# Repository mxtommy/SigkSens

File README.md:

# DEPRECEATED
# DEPRECEATED
Hi! This package does not have active maintenance. Please see [SensESP](https://github.com/SignalK/SensESP) for a more actively developed solution. :)
# DEPRECEATED
# DEPRECEATED

# SignalK Wifi Controllers
(Note: complete documentation is now available on the [Wiki page](https://github.com/mxtommy/SigkSens/wiki).)

## Design Goals
---------------------
Simple low cost Wifi based IoT device. Should be simple enough to setup/use that it could be manufactured and sold to people with no microcontroller/circuit design knowledge. Support configuration via a Web application, and network discovery for ease of use.

Assuming it will be installed close to the object being monitored/controlled, it should not need to support many IO by default. Aim to cover 80% of use cases with single device, assuming other 20% can be solved by adding a additional stand alone devices. If 80% of the time you only need 2 Inputs, the 20% of the time you need 4 inputs just put another device. IE prefer multiple cheap devices vs. one expensive do everything one.

Hardware should be easy to assemble on breadboard, as well as be able to be made into a PCB.

Device should send data to SignalK Server over Wifi.
Device should accept commands from Wifi. (WIP: how?)

## Use Case and Inputs required 
---------------------

- Engine Monitor
    - 1Wire Bus (multiple Temps)
    - 1 Digital Input (rpm pulse)
    - SHT30 (Engine room temp/humidity)
    - 1 Analog Inputs (Oil Presure)
- Bilge pump Monitor:
    - 2 Digital Input (Bilge pump on/off, High water Alarm)
- Fridge Monitor:
    - 1Wire Bus (Temps)
    - 1 Digital Input (Compressor on/off)
    - SHT30, Temp/Humidity
- Tank Monitor:
    - 1 Analog Input (Tank level)
- DC Monitor:
    - 1Wire Bus (Battery Temps)
    - 2 Analog Inputs - Current/Voltage 
- AC Monitor:
    - 2 Analog inputs - Current/Voltage
- GPS
    - UART
- Environment
    - Presure Sensor
    - IMU
    - SHT30 (temp/humidity)
        
## Final list of Inputs (and current status):
- 1Wire Bus (supporting MAX31850 Thermocouple breakout)
	- Done!
- MPU925X 9 axis IMU
	- Done!
- 2 Digital in (Opto isolated)
    - Done!
- 2 Digital out (Opto isolated)
	- Planned.
- SHT30 temp/humidity sensor
	- Done
- ADS1115 ADC (2 input 16 bits)
	- Done!
- Pressure sensor
	- Done!

## Requirement List

### Hardware
---------------------
- Circuits should follow best practices, over-voltage protection, isolated where possible, etc
	- Need to make friendly circuit diagrams (currentl in kicad, need to make images)
- Core Wifi Hardware module
    - 12V External Power
    - IO 
        - OneWire - Covers most Temp situations and can support many temp sensors in same bus. Only requires single resistor to support...
        - Config Reset button.
- Rest handled by adding to core. 
    - 2 opto Isolated Digital I/O
    - ADS1115 (16bit ADC)
    - INA219 (Current sensing)
    - IMU (Due to timing/computations needed, recommended to not run other sensors at same time as IMU)
    - SHT30 (Temp/Humidity)
    - Presure sensor

- Case/Physical connections.
    - 3d printable cases. 
    - Terminal blocks for connecting external wires.
    - Mounting of Core module and any expansion modules

### Software
----------------------

#### Features (and current status if not done)
- One binary to rule them all. (Should not need to recompile to support different sensors/functions) Saves supporting multiple versions of software.
- Wifi AP configuration. (Credentials not hard coded in source)
- Web API to support configuration via the webApp.
- No hardcoded configurations where possible. All config configurable via Webapp
- Configurations saved to filesystem.
- Supports discovery services (mDNS/ssdp)
- Non blocking interupts/timer mechanisms should be used instead of delay() whenever possible.
- Web based update of firmware.
	- [Over-the-air (OTA)](http://esp8266.github.io/Arduino/versions/2.0.0/doc/ota_updates/ota_updates.html)
      updates are supported using PlatformIO or Arduino IDE.
- Configurable user/pass for HTTP basic auth. 
	- Planned, not done yet.

#### Signalk
- Hosts a simple websocket only (no rest interface) signalk server. Responds to endpoint URL with URL of websocket, and hosts websocket server. Can handle one or two clients.
- Auto-discovers SignalK Server via mDNS. Can also be manually set. Connects to existing signalk server to push deltas there.
- Sends delta messages at regular (configurable) interval, combining multiple updates into one message when needed.

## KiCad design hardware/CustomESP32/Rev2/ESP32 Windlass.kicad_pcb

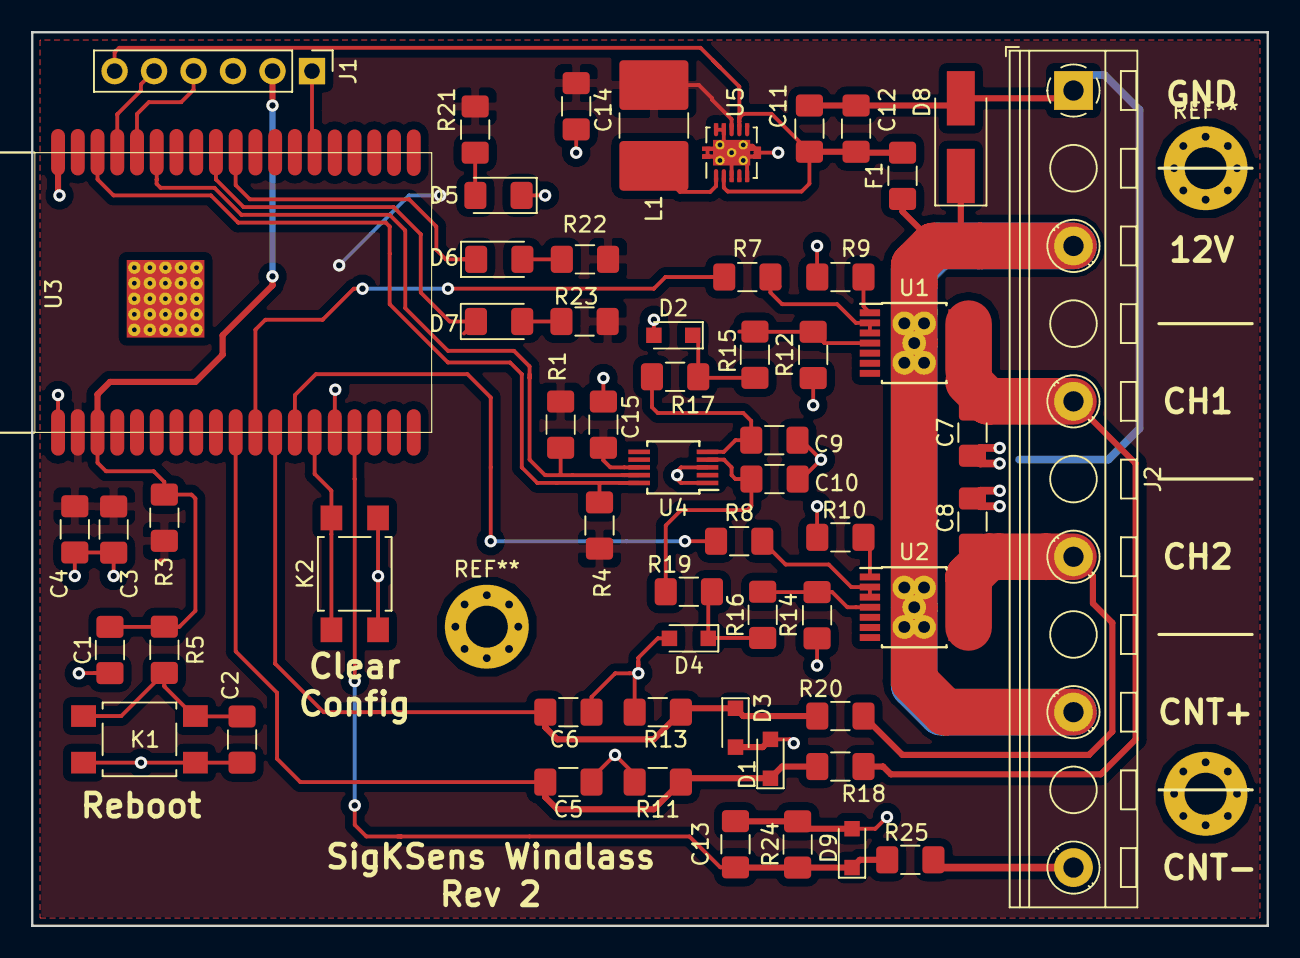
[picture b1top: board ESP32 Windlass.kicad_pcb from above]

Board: 2 copper layers, 79.5 x 57.5 mm, 58 parts (0 on the bottom side), 36 nets.

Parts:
C1, C2, C3, C15: 100nF; C_1206_3216Metric_Pad1.42x1.75mm_HandSolder
C4: 10uF; C_1206_3216Metric_Pad1.42x1.75mm_HandSolder
C5, C6, C9, C10, C13: 220pF; C_1206_3216Metric_Pad1.42x1.75mm_HandSolder
C7, C8, C11: 10nf; C_1206_3216Metric_Pad1.42x1.75mm_HandSolder
C12: 4.7uF/50V; C_1206_3216Metric_Pad1.42x1.75mm_HandSolder
C14: 47uf; C_1206_3216Metric_Pad1.42x1.75mm_HandSolder
D1, D2, D3, D4, D9: 3.3V; D_SOD-323_HandSoldering
D5: PWR_LED; LED_1206_3216Metric_Pad1.42x1.75mm_HandSolder
D6: LED_WIFI; LED_1206_3216Metric_Pad1.42x1.75mm_HandSolder
D7: LED_STATUS; LED_1206_3216Metric_Pad1.42x1.75mm_HandSolder
D8: SMAJ36CA; D_SMA_Handsoldering
F1: 450mA/48V; Fuse_1206_3216Metric_Pad1.42x1.75mm_HandSolder
J1: Conn_01x06; PinHeader_1x06_P2.54mm_Vertical
J2: Screw_Terminal_01x06; TerminalBlock_RND_205-00302_1x06_P10.00mm_Horizontal
K1: RESET; SW_SPST_TL3305A
K2: CFGRESET; SW_SPST_TL3305A
L1: 4.7uH; L_2816_7142Metric_Pad3.20x4.45mm_HandSolder
R1: 4.7K; R_1206_3216Metric_Pad1.42x1.75mm_HandSolder
R3, R11, R13, R24: 10k; R_1206_3216Metric_Pad1.42x1.75mm_HandSolder
R4, R7, R8, R15, R16, R17, R19: 4.7k; R_1206_3216Metric_Pad1.42x1.75mm_HandSolder
R5, R21, R22, R23: 470; R_1206_3216Metric_Pad1.42x1.75mm_HandSolder
R9, R10: 47; R_1206_3216Metric_Pad1.42x1.75mm_HandSolder
R12, R14: 3.3k 1%; R_1206_3216Metric_Pad1.42x1.75mm_HandSolder
R18, R20, R25: 1k; R_1206_3216Metric_Pad1.42x1.75mm_HandSolder
U1, U2: BTS7004-1EPP; Infineon_PG-TSDSO-14-22
U3: ESP32-WROVER
U4: ADS1015IDGS; MSOP-10_3x3mm_P0.5mm
U5: LM5166Y; Texas_S-PVSON-N10_ThermalVias

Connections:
+3V3: C3.2, C4.2, C14.1, C15.1, L1.2, R1.2, R3.2, R4.2, R21.2, R22.2, R23.2, U3.2, U4.8, U5.8
+12V: D8.1, F1.1, J2.2, J2.5, U1.15, U2.15
/CH1_EN: R7.1, U3.11
/CH1_LOAD: C7.1, J2.3, R18.2, U1.8
/CH1_SENSE: C9.1, R17.2, U4.5
/CH1_STATUS: C5.1, D1.1, R11.2, R18.1, U3.10
/CH2_EN: R8.1, U3.13
/CH2_LOAD: C8.1, J2.4, R20.2, U2.8
/CH2_SENSE: C10.1, R19.2, U4.4
/CH2_STATUS: C6.1, D3.1, R13.2, R20.1, U3.12
/COUNTER: C13.1, D9.1, R24.2, R25.1, U3.16
/COUNTER_IN: J2.6, R25.2
/IO0: J1.1, U3.25
/PROG_RST: C1.1, J1.2, R3.1, R5.2, U3.3
/RX0: J1.4, U3.34
/SCL: R4.1, U3.36, U4.10
/SDA: R1.1, U3.33, U4.9
/STATUS_LED: D7.1, U3.30
/TX0: J1.5, U3.35
/USB_VBUS: C11.1, C12.1, F1.2, J1.6, U5.2, U5.7
/WIFI_LED: D6.1, U3.29
GND: C1.2, C2.2, C3.1, C4.1, C5.2, C6.2, C7.2, C8.2, C9.2, C10.2, C11.2, C12.2, C13.2, C14.2, C15.2, D1.2, D2.2, D3.2, D4.2, D5.1, D8.2, D9.2, J1.3, J2.1, K1.2, K2.2, R9.1, R10.1, R11.1, R12.1, R13.1, R14.1, R24.1, U3.1, U3.15, U3.38, U3.39, U4.1, U4.3, U5.3, U5.5, U5.9, U5.10, U5.11
unnamed: C2.1, K1.1, R5.1
unnamed: D2.1, R15.2, R17.1
unnamed: D4.1, R16.2, R19.1
unnamed: D5.2, R21.1
unnamed: D6.2, R22.1
unnamed: D7.2, R23.1
unnamed: K2.1, U3.14
unnamed: L1.1, U5.1
unnamed: R7.2, U1.2, U1.3
unnamed: R8.2, U2.2, U2.3
unnamed: R9.2, U1.1
unnamed: R10.2, U2.1
unnamed: R12.2, R15.1, U1.4
unnamed: R14.2, R16.1, U2.4

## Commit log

2017-10-16 initial
2017-10-17 much progress, linked lists saved and loaded!
2017-10-17 reset config pin
2017-10-17 print pretty address
2017-10-19 Work
2017-11-02 stuff
2017-11-03 fix delay
2017-11-03 move onewire to iinterupt based
2017-11-03 cleanup
2017-11-11 major refactor, using Sensorinfo for all sensor types now
2017-11-13 more refactoring, but got it!
2017-11-14 timer customization!
2017-11-15 mpu925x
2017-11-17 mpu working
2017-11-20 websocket/sigk
2017-12-06 websocket and api work
2017-12-06 precision update
2017-12-29 Digital
2018-01-10 mpu work
2018-01-21 mpu calibration work
2018-01-21 LICENSE
2018-01-21 README/TODO
2018-01-21 renamed file to match directory
2018-01-22 refactor oneWire.ino -> oneWire.cpp
2018-01-22 moved configuration values into config.h
2018-01-23 gitignore for custom config
2018-01-23 Hardware info
2018-01-24 moar oneWire fixes
2018-01-24 split digitalIn.ino into separate .cpp and .h files
2018-01-27 Refactor Digital-in to be more flexible
2018-01-27 forgot to uncomment ifdef
2018-01-27 Update signalk to not initialize all variables on every loop
2018-01-28 refactor sensors
2018-01-28 refactor systemHz.ino
2018-01-28 my-config.h got renamed to my_config.h
2018-01-28 refactor configReset
2018-01-28 refactored websockets
2018-01-28 refactored signalK.ino
2018-01-28 refactor FSConfig
2018-01-28 refactor httpd.ino -> httpd.cpp
2018-01-29 OneWireSensorInfo
2018-01-29 SHT30SensorInfo
2018-01-29 MPU9250 and DigitalIn SensorInfo classes
2018-01-31 refactor SystemHzSensorInfo
2018-01-31 fix SensorInfo children instantiation
2018-02-01 make SensorInfo abstract
2018-02-01 create *SensorInfo::fromJson static methods
2018-02-02 make SensorType an enum
2018-02-02 Bonus: harmonize oneWire presence detection handling
2018-02-04 Start of ads1115
2018-02-04 Fix devide by zero exception
2018-02-04 remove isSerializable (obsolete)
2018-02-04 try to use mDNS to find the Signal K service if not defined
2018-02-04 selectively enable/disable digitalIn
2018-02-05 work on ads
2018-02-05 Work on ads1115
2018-02-05 selectively disable MPU
2018-02-05 conditionally enable sht30
2018-02-06 ADS1115 work
2018-02-06 Set offset/scale
2018-02-06 conditionally enable OneWire
2018-02-06 selectively enable websockets server
2018-02-07 Add ifdefs to ads1115
2018-02-07 Fix bug pushing empty updates
2018-02-07 Timers for ads1115
2018-02-07 Fix Timers
2018-02-07 implement support for the BMP280 pressure sensor
2018-02-08 Fix ads1115 in i2c
2018-02-08 Add Libraries used
2018-02-09 Prepare to Save cal to sensorinfo.
2018-02-10 Ok maybe not in sensorInfo, use FS
2018-02-10 globally renamed sensorList -> sensorStorage
2018-02-10 set key attributes in SensorInfo constructors
2018-02-10 implement forEach
2018-02-10 re-remove SensorInfo::key
2018-02-10 split sensor storage into sensor type specifc sublists
2018-02-10 implement SensorStorage that is compatible with sensorList
2018-02-10 use sensorStorage.find in i2c
2018-02-10 formatting fixes
2018-02-10 use SensorInfo::find when querying by address
2018-02-10 fix bmp280 polling
2018-02-10 switch from LinkedList to std::map
2018-02-10 loop SensorInfo with forEach instead of get
2018-02-10 remove SensorStorage::get
2018-02-10 added ArduinoSTL to Libraries folder
2018-02-10 removed unused LinkedList folder
2018-02-10 change http server library
2018-02-10 make getSensorInfo stream its output
2018-02-10 add ESPAsyncTCP and ESPAsyncWebServer to Libraries
2018-02-10 Update for refactor
2018-02-11 Accel/Gyro Cal
2018-02-11 Magnetic Calibration :D
2018-02-11 Fix Filter rate calc
2018-02-16 Switch to Interrupt based, get rid of modes
2018-02-16 make MPU9250 interrupt pin configurable
2018-02-17 Hertz and pulse count!
2018-02-18 create external interrupt ISRs with lambdas
2018-02-18 DC Monitor Circuit
2018-02-20 Start of AnalogIn
2018-02-20 New global timer for sending deltas
2018-02-20 Save timers and MPU rework
2018-02-20 Refactor SHT30
2018-02-20 Refactor BMP
2018-02-20 Refactor ads1115
2018-02-20 Refactor DigitalIn
2018-02-20 Refactor oneWire
2018-02-21 Finish up Analog in
2018-02-21 Usage Update
2018-02-21 BMP Scale/Offset and filter
2018-02-21 Fix GetSensorInfo
2018-02-22 Start of DigitalOut
2018-02-22 Init Pins
2018-02-22 Config reset via http
2018-02-24 Start to receive deltas
2018-02-24 Working on Digital out
2018-02-24 Fix HTTP to use flags. Async doesn't like doing stuff in the requests)
2018-02-26 Digital Out State done!
2018-02-27 Usage update!
2018-03-08 convert oneWire to Reactduino
2018-03-08 convert main loop to Reactduino
2018-03-10 converted BMP280 and ADS1115 to Reactduino
2018-03-10 convert SHT30 to reactduino
2018-03-10 convert MPU9250 to reactduino
2018-03-11 update BMP280 Json format
2018-03-11 made the SystemHz sensor optional
2018-03-11 make httpGetSensorInfo use SensorInfo::toJson
2018-03-11 convert digitalIn to Reactduino
2018-03-11 update oneWire Json format
2018-03-11 add attr names and values to sensor json output
2018-03-11 convert httpd and webSocket to Reactduino
2018-03-11 SignalK calling goes through Reactduino
2018-03-11 update the remaining sensors to use Reactduino, make the slow update delay configurable
2018-03-11 update sensor Json formats
2018-03-11 removed obsolete timer.cpp and timer.h
2018-03-12 removed obsolete timer.cpp and timer.h
    Removed support for setting delta timer (because it would be
    inconvenient in Reactduino).
2018-03-16 Add Reactduino to Libraries
2018-05-16 Add timeout to wifi connection
2018-05-19 fix some bugs
2018-05-29 Move sketch to appropriately named subfolder
    The Arduino IDE requires that a sketch be located in a folder of the same name. Although the name of the repository does match the sketch name, when GitHub's popular Clone or download > Download ZIP 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
    When opening a file that does not meet this sketch/folder name matching requirement the Arduino IDE presents a dialog:
    The file "SigkSens.ino" needs to be inside a sketch folder named "SigkSens".
    Create this folder, move the file, and continue?
    After clicking "OK" the Arduino IDE currently moves only the file SigkSe
2018-07-22 Feature: Enable AnalogIn
2018-07-22 Update USAGE.md
    Add description how to enable analogIn
2018-07-22 Update httpd.cpp
    Add line change in debug msg
2018-07-24 Support Tokens
2018-07-27 Add more interesting index page, check wifi connection, suppress empty sensor updates
2018-07-31 disable all sensors by default
2018-07-31 SHT/MPU moved to subdir
2018-07-31 oneWire dir
2018-07-31 bmp280 dir
2018-07-31 ads1115 dir
2018-08-01 digitalIn dir
2018-08-01 digitalOut dir
2018-08-01 analogIn dir
2018-08-01 systemHz dir
2018-08-01 move http and websocket to dir
2018-08-01 save 1K of ram with F Macro (Keep constant strings out of ram)
2018-08-01 Fix header files. includes in cpp file :)
2018-08-01 strip getsensor* stuff
2018-08-01 Nuke ADS1115 read timer set (why would it ever change?
2018-08-02 some small fixes
2018-08-02 Fix SensorType_MAX
2018-08-03 comment out sensors by default
2018-08-03 websocket to reactduino (so it's not called only ever 200ms)
2018-08-03 Fix capatilization for linux
2018-08-09 Default Path for systemhz, and set it to 1/sec update
2018-08-09 cleanup httpd.cpp
2018-08-09 Move configReset and discovery stuff to directories
2018-08-09 Move sigk service to directory
2018-08-11 More cleanup. Move wifi to own file
2018-08-16 Add PlatformIO relevant files to .gitignore
2018-08-16 support the main DallasTemperature library as well
2018-08-16 use send_P to send a string from program memory
2018-08-16 updated directory layout to be compatible with both Arduino IDE and PlatformIO
2018-08-16 add a basic platformio.ini file
2018-08-16 make HTTP port configurable in config.h
2018-08-22 re-enable getSensorInfo sensor contents
2018-08-22 disable debug printing of deltas
2018-08-22 "if in doubt, reset"
2018-08-22 add an uptime local sensor
2018-08-22 make config portal timeout length a config parameter
2018-08-26 Renable getSensorInfo + make serial deltas configurable
2018-08-27 Tiny change to test my GitHub setup
2018-09-15 Add LED blinking status indication
2018-09-19 Cleanup compiler warnings
2018-09-19 Move libraries to zip files
2018-09-19 Stop running if no SPIFFS
2018-09-19 Make it easier to troubleshoot mDNS/see which server you are connected to
2018-09-19 move sensorStorage stuff out of sigksens.h
2018-09-19 http callbacks! Moved MPU stuff to it's own file!
2018-09-19 oops forgot a debug print :)
2018-09-25 Add pointer to the Wiki page at the top
2018-09-26 Fix sht30 scale/offset
2018-09-26 naming fix
2018-09-26 get rid of /setTimerDelay as no longer used
2018-10-02 Invert Digital Input logic level + typo
2018-10-07 fixed a typo in filename
2018-10-09 implement OTA support
2018-10-14 add ReactESP zip in the Libraries folder
2018-10-14 use ReactESP instead of Reactduino
2018-10-16 functional ISR creation
2018-10-25 Clean up DigIn comments in config.h. Also set a default OTA password.
2018-11-18 ESP32 WIP
2018-11-20 setup esp32 platformio
2018-11-20 cleanup user_interface
2018-11-20 Fix discovery.cpp
2018-11-20 work on ssdp
2018-11-21 some updates to pcb
2018-11-21 ESP32 compiling! :) (not esp8266 though)
2018-11-26 Rev2
2018-11-30 Format SPIFFS if not formated
2018-12-14 use fixed uSSDP
2018-12-20 start of windlass stuff
2018-12-20 WROVER Pins
2018-12-24 make the platformio setup default to Wemos D1 Mini
2018-12-26 Update to use branch
2018-12-27 configStore
2018-12-27 Move LedBlinker to it's own class file. Fix systemHz using configStore
2018-12-27 Replace LED_BUILTIN with LED_PIN
    Because not all ESP32 boards have a defined LED_BUILTIN.
2018-12-27 LED_BUILTIN fix
    Not all ESP32 boards have a defined LED_BUILTIN.
2019-01-01 SignalK Service rewrite
2019-01-01 SystemHz refactor
2019-01-01 Fix use of String in ssdp (needs char)
2019-01-02 Fix Bool deltas
2019-01-02 Request Auth stuff :)
2019-01-02 start getting rid of FSConfig
2019-01-02 move stuff to new components DIR
2019-01-06 Some HTTP work
2019-01-06 Change format of configStore
2019-01-06 new HTTP webpage and config setting API :D
2019-01-06 some html stuff
2019-01-06 ArduinoIDE can't support paths relative to sketch folder like PlatformIO
2019-01-06 Simple Tank Level
2019-01-06 save 1k of ram
2019-01-06 fix ssdp on esp8266
2019-01-06 update uSSDP to fix memory leak
2019-01-11 sensorComponent start
2019-01-11 Start of registry
2019-01-12 ComponentSensor Class :)
2019-01-12 http get/set
2019-01-13 Fix :)
2019-01-15 Set component config,getSensorInfo
2019-01-15 rework simpleTankLevel
2019-02-16 Update for Butch :)
2019-02-17 Update firmware over HTTP :)
2019-04-01 move to refactor
2019-04-02 WIP digitalSwitch
2019-04-04 ADS :)
2019-04-04 Fix channel
2019-04-04 DigitalSwitch Works :D
2019-04-05 WIP :)
2019-05-01 Start of BilgeMon
2019-05-01 BilgeMon
2019-05-11 wip 1w
2019-05-22 Delete Mk2.jpg
    Wrong photo
2019-05-24 OneWire/esp8288 fix/ engineMon start
2019-05-24 sht30 :)
2019-05-27 Enginemon
2019-07-18 fix duplicate file in repo
2019-07-19 update wifimanager version
2019-12-20 A version of the uSSDP library that compiles.
2020-02-17 Add support for BME280 sensor
2020-02-17 Move sea level pressure config to config.h
2020-02-17 Modify sea level config line
2020-02-20 Update default path for systemhz
2020-07-05 Added support for INA219 current sensor
